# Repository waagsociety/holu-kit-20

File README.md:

# holu-kit-20
Hollandse Luchten sensor kit, version 2.0.

This repo has the scope to host the source files of the HoLu kit v2.
In the repo there are:
- sketches for basic and extended HoLu kit
- 3D model of the case
- pcb files and images
- BOM

Some extra information:
- Assembling manual of the HoLu kit: https://hollandseluchten.waag.org/wp-content/uploads/sites/9/HOLU_manual_English.pdf
- Parts descriptions: https://hollandseluchten.waag.org/holu-sensorkit/
- Troubleshooting: https://hollandseluchten.waag.org/veelgestelde-vragen/

In this repo you also find the presentations related to the HoLu kit, the slides have been used during internal meetings and meet-up with the participants of the projects.

Missing:
- ~~3D model of the moulds~~: the 3D models of the moulds were designed by the company that produced the casings, the moulds are based on the original 3D models you find in this repo.
- 2D model internal acrylic plate.

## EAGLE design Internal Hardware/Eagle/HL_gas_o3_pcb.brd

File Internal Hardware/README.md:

## Hardware - holu-kit-20

Hollandse Luchten sensor kit, version 2.0.

In this folder you find the digital files for the pcbs production used to connect the different modules of the HoLu kit v2.

The Eagle files are the design files of the printed circuit boards. The basic HoLu kit includes:
- HL_sensors_pcb_all (schematic and layout)
- HL_Interface_pcb (schematic and layout)
- hl_bme280_out_pcb (schematic and layout)

The extended HoLu kit has all the modules mentioned above and also the following ones:
- HL_gas_no2_pcb (schematic and layout)
- HL_gas_o3_pcb (schematic and layout)

The Gerber files were submitted to the out-sourced service that produced the 200 HoLu kits boards.
The boards were produced by https://jlcpcb.com/.

The images below show the boards and the components that populate them. The components specifications can be found in the BOM

## Sensors pcb top view
### Basic

| pcbs  | component locations | populated pcb |
| ------------- | ------------- | ----------|
|  |  |  |

Components:
- JP1
- JP2
- J_PM25
- J_TH_IN

### Extended

| pcbs  | component locations | populated pcb |
| ------------- | ------------- | ----------|
|  |  |  |

Components:
- JP1
- JP2
- J_PM25
- J_TH_IN
- J_GAS_NO2
- J_GAS_O3

## Sensors pcb bottom view
### Basic

| pcbs  | component locations | populated pcb |
| ------------- | ------------- | ----------|
|  |  |  |

### Extended

| pcbs  | component locations | populated pcb |
| ------------- | ------------- | ----------|
|  |  |  |

Components:
- Q1, Q2
- R1, R2, R3, R4

### Interface pcb top view
## Basic and Extended

| pcbs  | component locations | populated pcb |
| ------------- | ------------- | ----------|
|  |  |  |

Components:
- SW_RST
- SW_CONFIG
- R3, R4
- C1
- LED1

## Interface pcb bottom view
### Basic and Extended

| pcbs  | component locations | populated pcb |
| ------------- | ------------- | ----------|
|  |  |  |

Components:
- JP_12
- JP_16

## BME pcb top view
### Basic and Extended

| pcbs  | component locations | populated pcb |
| ------------- | ------------- | ----------|
|  |  |  |

Components:
- J_TH

## BME pcb bottom view
### Basic and Extended

| pcbs  | component locations | populated pcb |
| ------------- | ------------- | ----------|
|  |  |  |

Components:
- J_G

## GAS pcbs top view
### Extended

| pcbs  | component locations | populated pcb |
| ------------- | ------------- | ----------|
|  |   |  |

Components:
- J_GAS
- J_ADS115

## GAS pcbs bottom view
### Extended

| pcbs  | component locations | populated pcb |
| ------------- | ------------- | ----------|
|  |    |  |

Components:
- J_O3
- C1, C2

## EXTRA
### Internal plate
The HoLu kit uses an acrylic plate to hold the sensors and the electronic parts in place. The plates were cut in the Fablab at De Waag.

### Feather M0 with RFM95 LORA Radio

It is important to buy the Feather M0 Lora with headers because the connectors that are usually provided attached to the board are too short for this application.
It is necessary to use the long staking headers, see BOM. It is also necessary to solder the coaxial connector for the antenna to the board.
You can find the instruction at this link: https://learn.adafruit.com/adafruit-feather-m0-radio-with-rfm69-packet-radio/antenna-options.

### Adalogger Feather

On this module it is necessary to solder the female connector and insert the battery and the SD-card, https://learn.adafruit.com/adafruit-adalogger-featherwing.

### Temperature and Humidity Sensor
The sesnor selected to measure temperature and humidity is the sensor BME280 from Bosh: https://www.bosch-sensortec.com/products/environmental-sensors/humidity-sensors-bme280/.

Due to tools limitation, the sensor has been deployed on a low cost breakout board:

**NOTE**: During the on the field deployment of the HoLu kits, we observed that temperature sensor BME280 module is too fragile for such application and after a while many it tends to break. The Extended HoLu kit requires the temp/hum sensor for the calibration of the gas sensors so we adopted a different breakout board with the same sensor, the module provided by Adafruit, https://www.adafruit.com/product/2652.

To better protect the module inside the HoLu kit enclosure, it has been located in a more central place inside the casing.

If you are interested on the connection between the extra module, please open an issue in the issue section.

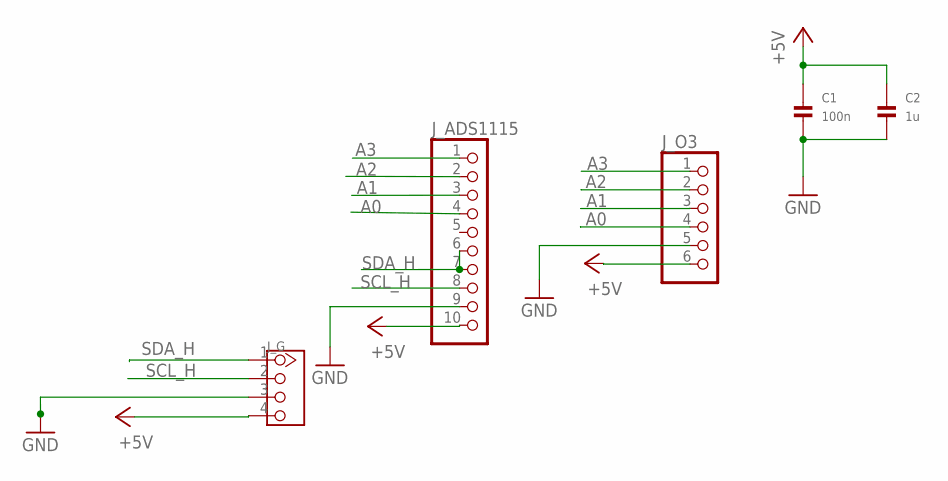
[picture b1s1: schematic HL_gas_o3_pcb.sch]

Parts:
C1: 100n; 1206
C2: 1u; 1206
J_ADS1115: HEADER-1X10; 1X10_OVAL
J_G: TWIG-4P-2.0-2.0; 4P-2.0
J_O3: HEADER-1X6; 1X06_OVAL

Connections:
+5V: C1.1, C2.1, J_ADS1115.10, J_G.4, J_O3.6
A0: J_ADS1115.4, J_O3.4
A1: J_ADS1115.3, J_O3.3
A2: J_ADS1115.2, J_O3.2
A3: J_ADS1115.1, J_O3.1
GND: C1.2, C2.2, J_ADS1115.9, J_G.3, J_O3.5
SCL_H: J_ADS1115.8, J_G.2
SDA_H: J_ADS1115.6, J_ADS1115.7, J_G.1

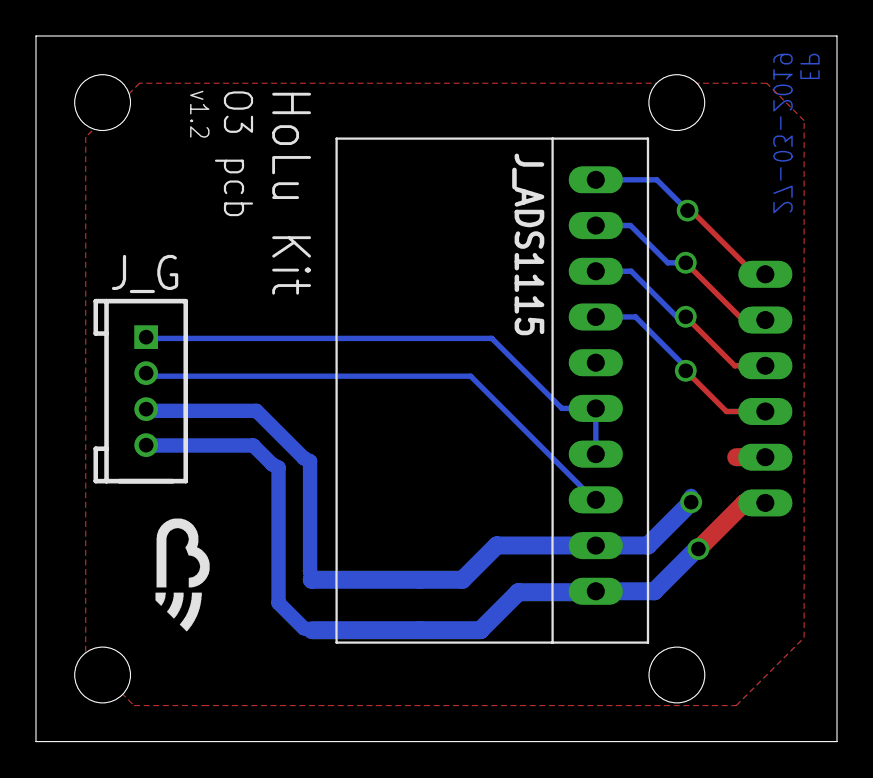
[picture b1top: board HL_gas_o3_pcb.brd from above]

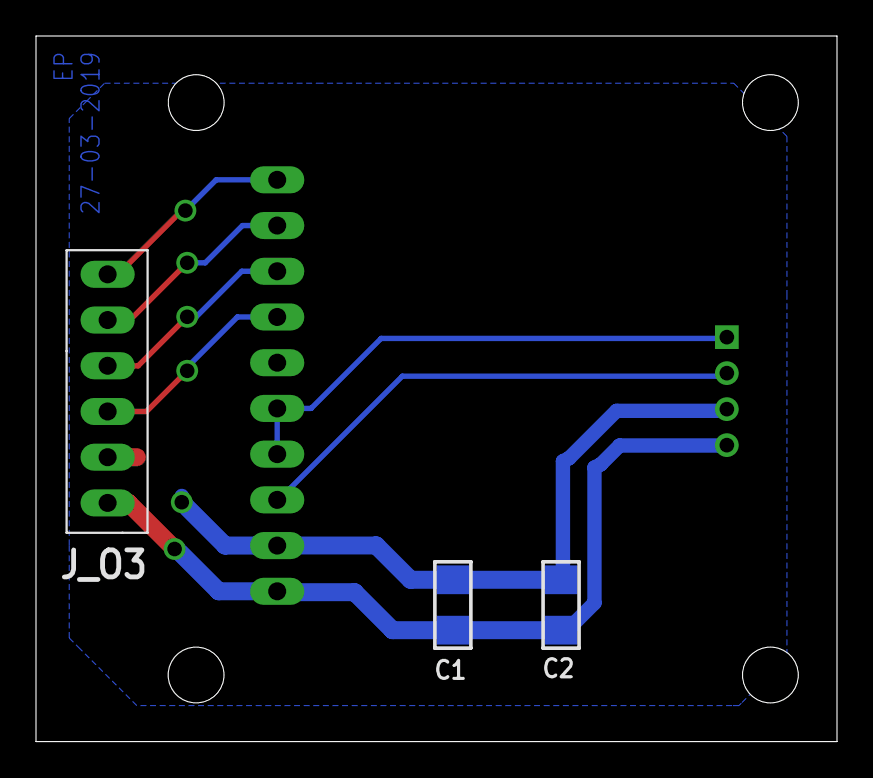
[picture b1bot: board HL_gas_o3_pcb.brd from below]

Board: 2 copper layers, 44.5 x 39.2 mm, 5 parts (2 on the bottom side), 8 nets.

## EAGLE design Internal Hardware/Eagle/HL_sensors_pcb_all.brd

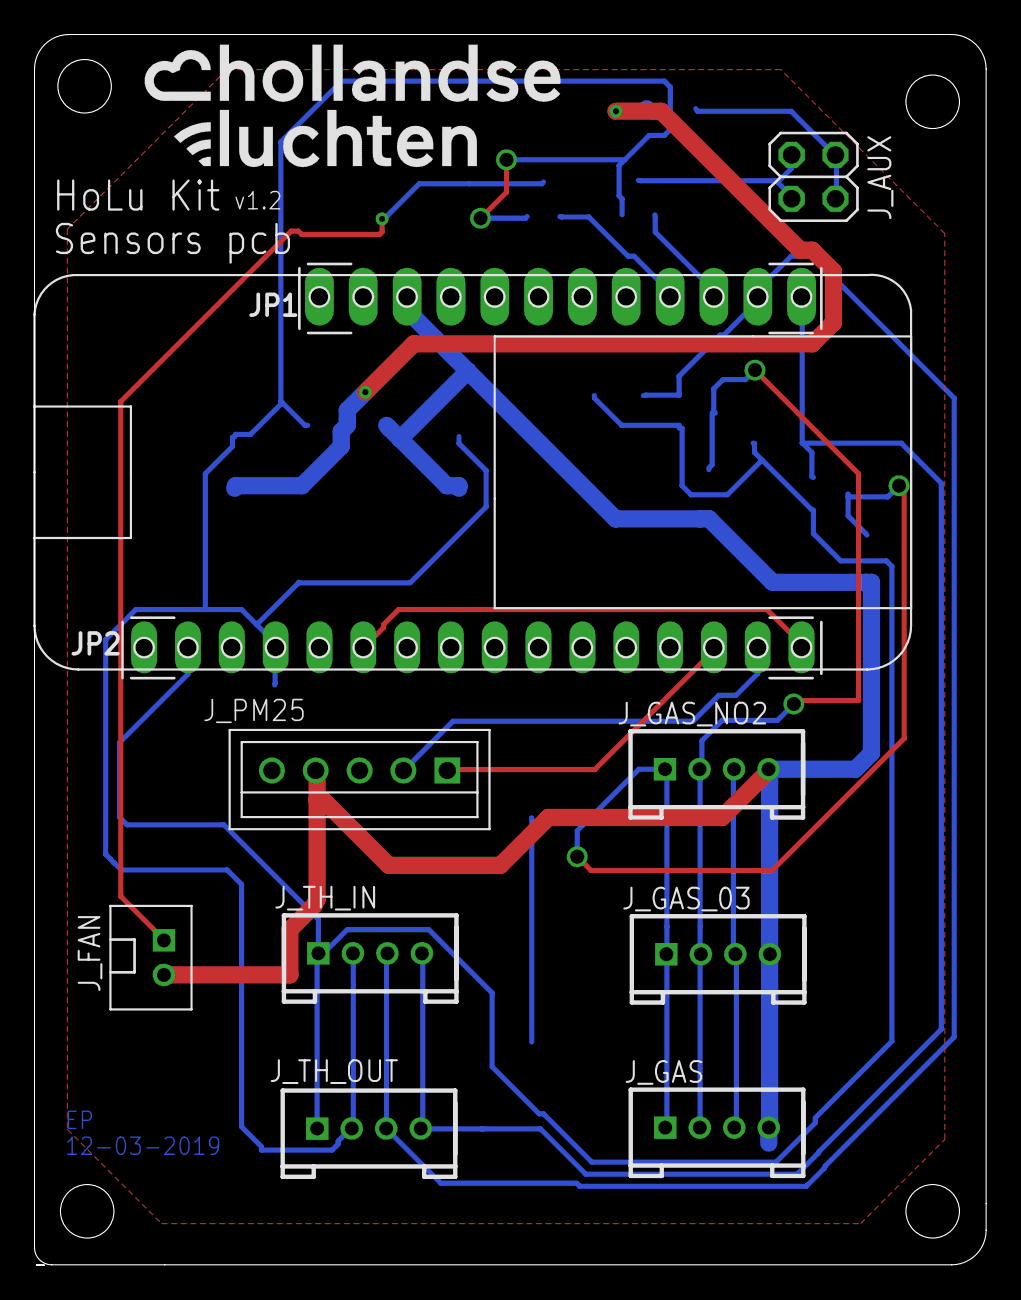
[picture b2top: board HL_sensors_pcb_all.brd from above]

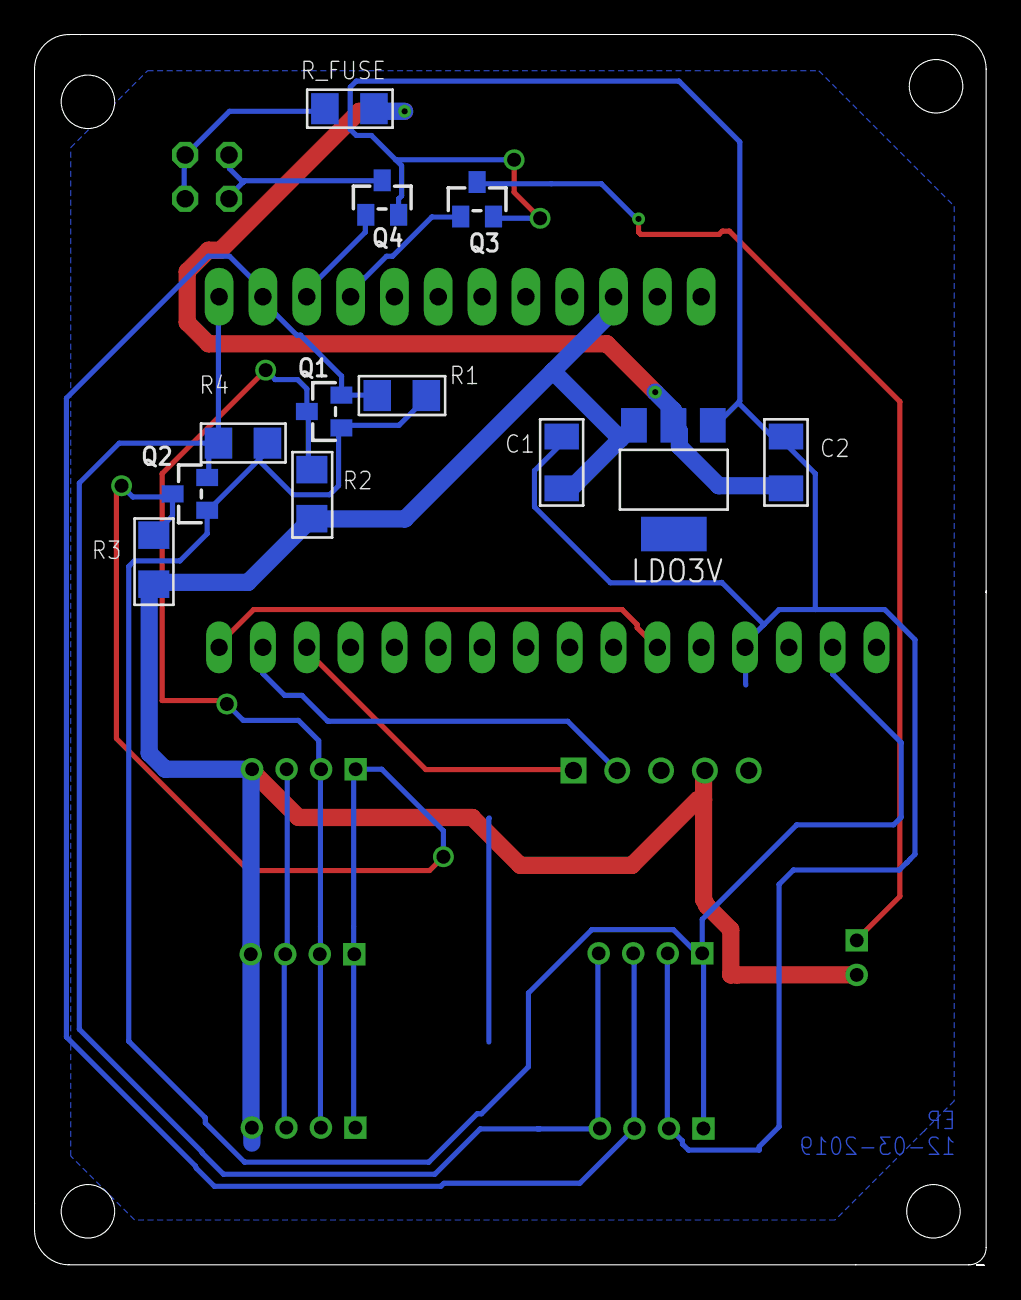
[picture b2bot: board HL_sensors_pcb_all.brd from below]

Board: 2 copper layers, 55.1 x 71.3 mm, 23 parts (12 on the bottom side), 16 nets.

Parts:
C1, C2: 1u; C1206K
JP1: 1X12_OVAL
JP2: 1X16_OVAL
J_AUX: 2X02
J_FAN: JST-2.0
J_GAS: 4P-2.0
J_GAS_03: 4P-2.0
J_GAS_NO2: 4P-2.0
J_TH_IN: bme820; 4P-2.0
J_TH_OUT: bme820; 4P-2.0
LDO3V: REG1117; SOT223
Q1, Q2, Q3, Q4: SOT23-WIDE
R1, R2, R3, R4: 10k; 1206
R_FUSE: 10k; 1206
U$1: ADA_FEATHER_NOPADS
X2: J_PM25; B5B-XH

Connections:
+3V3: JP2.2, J_TH_IN.1, J_TH_OUT.1, Q1.1, Q2.1, R1.2, R4.2
+5V: C1.1, JP1.3, J_FAN.2, J_GAS.4, J_GAS_03.4, J_GAS_NO2.4, LDO3V.3, R2.2, R3.2, X2.P$4
GND: C1.2, C2.2, JP2.4, J_GAS.3, J_GAS_03.3, J_GAS_NO2.3, J_TH_IN.2, J_TH_OUT.2, LDO3V.1, Q3.2, Q4.2, X2.P$3
unnamed: J_FAN.1, Q3.3
unnamed: J_AUX.1, J_AUX.3, Q4.3
unnamed: J_AUX.2, J_AUX.4, R_FUSE.1
unnamed: JP2.6, JP2.16
RX: JP2.14, X2.P$1
SCL: JP1.11, J_TH_IN.3, J_TH_OUT.3, Q1.2, R1.1
SCL_H: J_GAS.2, J_GAS_03.2, J_GAS_NO2.2, Q1.3, R2.1
SDA: JP1.12, J_TH_IN.4, J_TH_OUT.4, Q2.2, R4.1
SDA_H: J_GAS.1, J_GAS_03.1, J_GAS_NO2.1, Q2.3, R3.1
TX: JP2.15, X2.P$2
VCC: C2.1, LDO3V.2, R_FUSE.2
V_FAN: JP1.9, Q3.1
V_HEAT: JP1.10, Q4.1

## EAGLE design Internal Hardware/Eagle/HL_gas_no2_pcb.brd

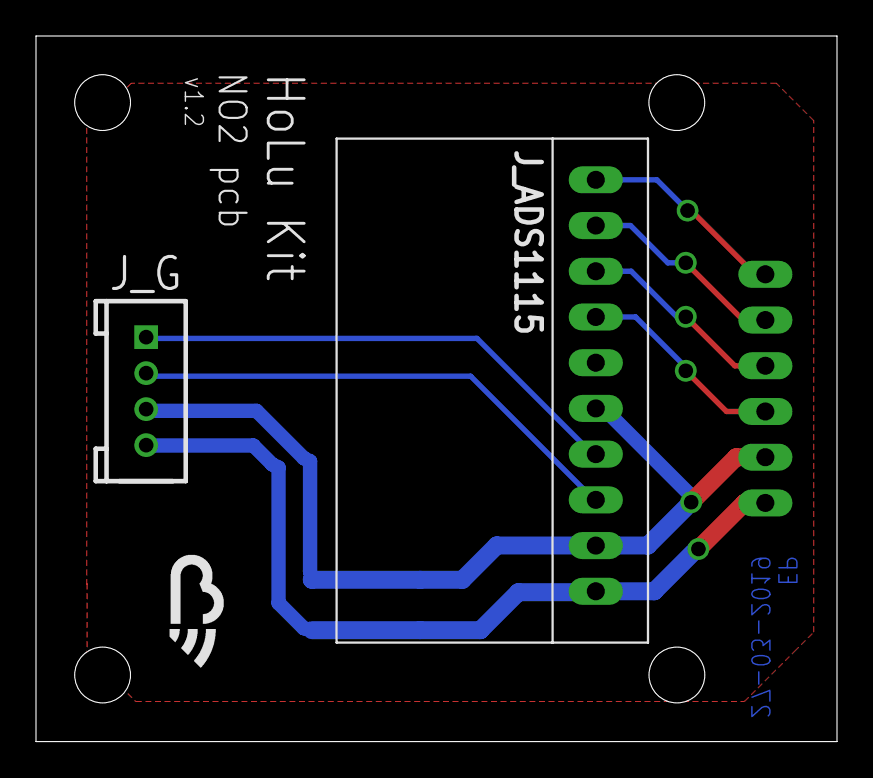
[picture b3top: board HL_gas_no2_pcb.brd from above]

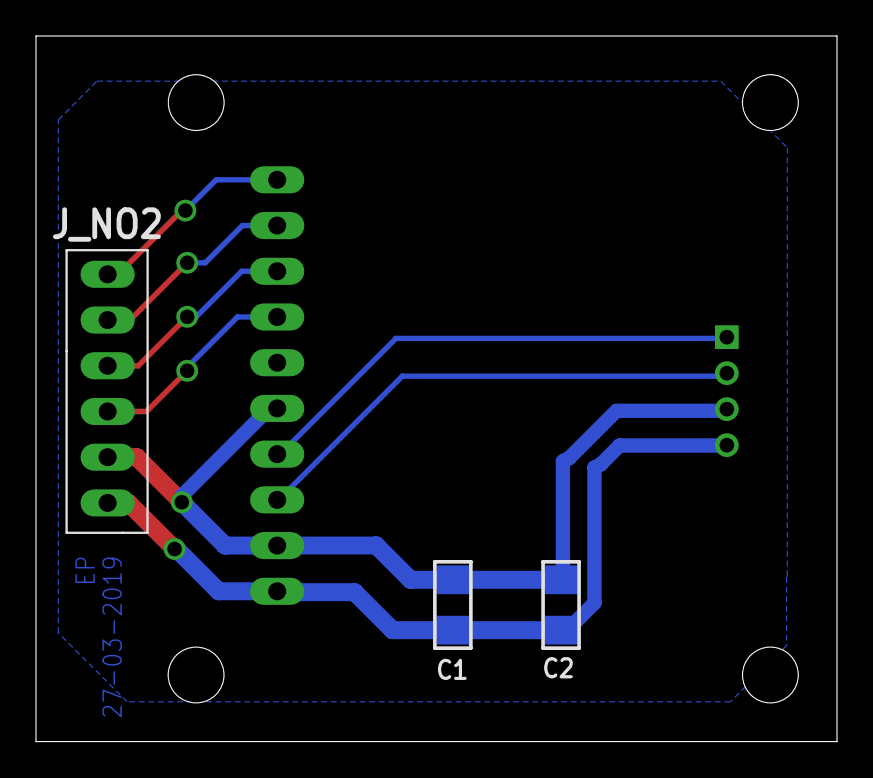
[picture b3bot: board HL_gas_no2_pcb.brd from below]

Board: 2 copper layers, 44.5 x 39.2 mm, 5 parts (2 on the bottom side), 8 nets.

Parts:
C1: 100nF; 1206
C2: 1uF; 1206
J_ADS1115: 1X10_OVAL
J_G: 4P-2.0
J_NO2: 1X06_OVAL

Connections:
+5V: C1.1, C2.1, J_ADS1115.10, J_G.4, J_NO2.6
A0: J_ADS1115.4, J_NO2.4
A1: J_ADS1115.3, J_NO2.3
A2: J_ADS1115.2, J_NO2.2
A3: J_ADS1115.1, J_NO2.1
GND: C1.2, C2.2, J_ADS1115.6, J_ADS1115.9, J_G.3, J_NO2.5
SCL_H: J_ADS1115.8, J_G.2
SDA_H: J_ADS1115.7, J_G.1

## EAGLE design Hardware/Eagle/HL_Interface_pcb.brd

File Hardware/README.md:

# Hardware - holu-kit-20

Hollandse Luchten sensor kit, version 2.0.

In this folder you find the digital files for the pcbs production used to connect the different modules of the HoLu kit v2.

The Eagle files are the design files of the printed circuit boards. The basic HoLu kit includes:
- HL_sensors_pcb_all (schematic and layout)
- HL_Interface_pcb (schematic and layout)
- hl_bme280_out_pcb (schematic and layout)

The extended HoLu kit has all the modules mentioned above and also the following ones:
- HL_gas_no2_pcb (schematic and layout)
- HL_gas_o3_pcb (schematic and layout)

The Gerber files were submitted to the out-sourced service that produced the 200 HoLu kits boards.
The boards were produced by https://jlcpcb.com/.

The images below show the boards and the components that populate them. The components specifications can be found in the BOM

## Sensors pcb top view
### Basic

| pcbs  | component locations | populated pcb |
| ------------- | ------------- | ----------|
|  |  |  |

Components:
- JP1
- JP2
- J_PM25
- J_TH_IN

### Extended

| pcbs  | component locations | populated pcb |
| ------------- | ------------- | ----------|
|  |  |  |

Components:
- JP1
- JP2
- J_PM25
- J_TH_IN
- J_GAS_NO2
- J_GAS_O3

## Sensors pcb bottom view
### Basic

| pcbs  | component locations | populated pcb |
| ------------- | ------------- | ----------|
|  |  |  |

### Extended

| pcbs  | component locations | populated pcb |
| ------------- | ------------- | ----------|
|  |  |  |

Components:
- Q1, Q2
- R1, R2, R3, R4

### Interface pcb top view
## Basic and Extended

| pcbs  | component locations | populated pcb |
| ------------- | ------------- | ----------|
|  |  |  |

Components:
- SW_RST
- SW_CONFIG
- R3, R4
- C1
- LED1

## Interface pcb bottom view
### Basic and Extended

| pcbs  | component locations | populated pcb |
| ------------- | ------------- | ----------|
|  |  |  |

Components:
- JP_12
- JP_16

## BME pcb top view
### Basic and Extended

| pcbs  | component locations | populated pcb |
| ------------- | ------------- | ----------|
|  |  |  |

Components:
- J_TH

## BME pcb bottom view
### Basic and Extended

| pcbs  | component locations | populated pcb |
| ------------- | ------------- | ----------|
|  |  |  |

Components:
- J_G

## GAS pcbs top view
### Extended

| pcbs  | component locations | populated pcb |
| ------------- | ------------- | ----------|
|  |   |  |

Components:
- J_GAS
- J_ADS115

## GAS pcbs bottom view
### Extended

| pcbs  | component locations | populated pcb |
| ------------- | ------------- | ----------|
|  |    |  |

Components:
- J_O3
- C1, C2

## EXTRA
### Feather M0 with RFM95 LORA Radio

It is important to buy the Feather M0 Lora with headers because the connectors that are usually provided attached to the board are too short for this application.
It is necessary to use the long staking headers, see BOM. It is also necessary to solder the coaxial connector for the antenna to the board.
You can find the instruction at this link: https://learn.adafruit.com/adafruit-feather-m0-radio-with-rfm69-packet-radio/antenna-options.

### Adalogger Feather

On this module it is necessary to solder the female connector and insert the battery and the SD-card, https://learn.adafruit.com/adafruit-adalogger-featherwing.

**NOTE**: During the on the field deployment of the HoLu kits, we observed that temperature sensor BME280 module is too fragile for such application and after a while many it tends to break. The Extended HoLu kit requires the temp/hum sensor for the calibration of the gas sensors so we adopted a different breakout board with the same sensor, BME280, see "link to issue web page".

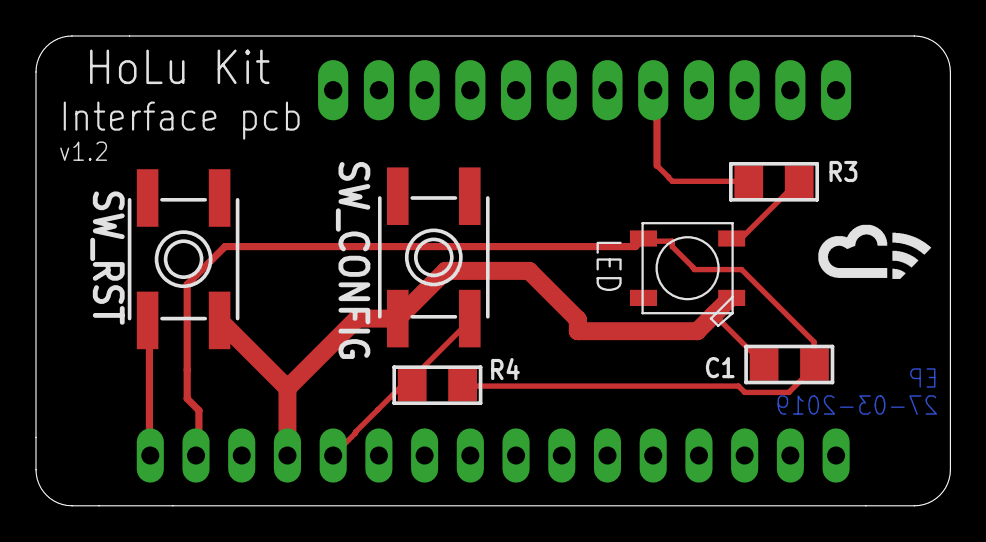
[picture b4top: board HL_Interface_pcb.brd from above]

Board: 2 copper layers, 50.8 x 26.1 mm, 8 parts (0 on the bottom side), 6 nets.

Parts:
C1: 0.1u; 1206
JP_12: 1X12_OVAL
JP_16: 1X16_OVAL
LED: WS2812B5050; WS2812B
R3: 470; 1206
R4: 10K; 1206
SW_CONFIG: EVQ-Q2
SW_RST: EVQ-Q2

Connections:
+3V3: C1.1, JP_16.2, LED.1-VDD, R4.2
GND: C1.2, JP_16.4, LED.3-GND, SW_CONFIG.A', SW_RST.A
LED_IN: JP_12.8, R3.1
unnamed: LED.4-DIN, R3.2
V_CONF: JP_16.5, R4.1, SW_CONFIG.B'
V_RST: JP_16.1, SW_RST.B

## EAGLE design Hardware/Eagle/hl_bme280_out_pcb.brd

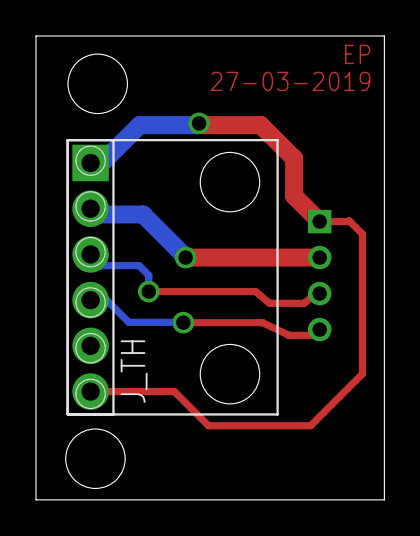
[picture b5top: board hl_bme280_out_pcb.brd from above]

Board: 2 copper layers, 19.4 x 25.8 mm, 3 parts (1 on the bottom side), 4 nets.

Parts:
J_G: 4P-2.0
J_TH: 6P-2.54-80/40MIL
U$1: BME280_BO_NOPADS

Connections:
+3V3: J_G.1, J_TH.1, J_TH.6
GND: J_G.2, J_TH.2
SCL: J_G.3, J_TH.3
SDA: J_G.4, J_TH.4

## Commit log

2020-01-29 access check
2020-01-29 basic code and ignore
2020-01-29 extended sketch - 3d model
2020-02-28 update hardware and BOM
2020-03-02 hardware images
2020-03-03 hardware/casing
2020-03-03 hardware main image
2020-03-03 kits image
2020-03-06 add slides holukit
2020-03-09 HL data infrastructure and Lora Network - Hollandse Helden Training
2020-04-21 update bme280
2020-11-03 images for forum

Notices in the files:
Hardware/Eagle/HL_Interface_pcb.brd:
Released under the Creative Commons Attribution Share-Alike 4.0 Licence
https://creativecommons.org/licenses/by-sa/4.0
parts and their libraries:
microbuilder: This work is placed in the public domain, and may be freely used for commercial and non-commercial work with the following conditions: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
